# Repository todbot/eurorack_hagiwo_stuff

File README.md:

# eurorack_hagiwo_stuff

So far just a PCB version of ["additive_vco"](https://note.com/solder_state/n/n30b3a8737b1e)

Here's a little demo video of it in action:

https://user-images.githubusercontent.com/274093/197078909-dfc56eac-acbd-4a94-ae75-ff46f5945844.mp4

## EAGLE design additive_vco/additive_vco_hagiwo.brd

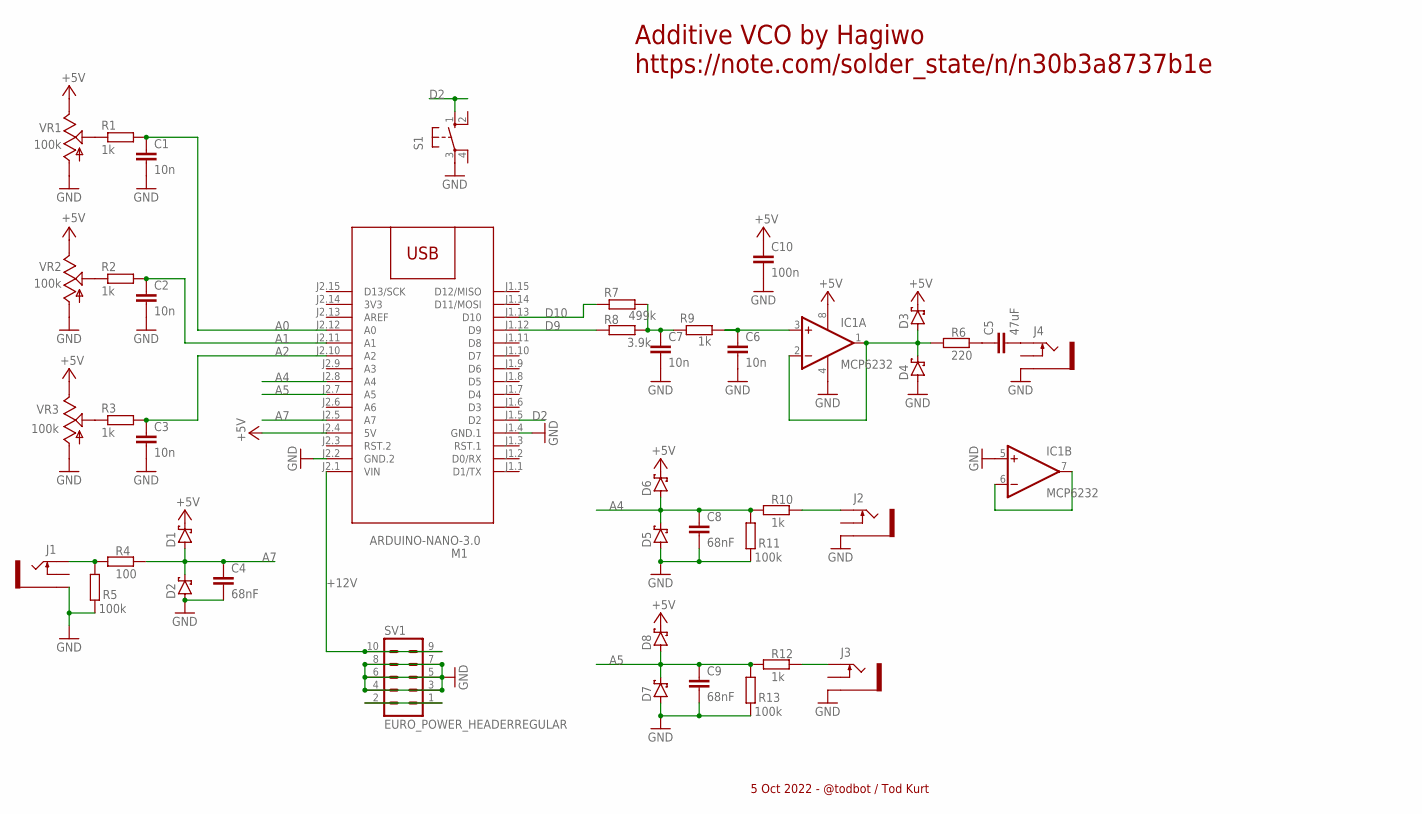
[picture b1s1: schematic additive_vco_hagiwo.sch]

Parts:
C1, C2, C3, C6, C7: 10n; C025-025X050
C4, C8, C9: 68nF; C025-025X050
C5: 47uF; C025-025X050
C10: 100n; C025-025X050
D1, D2, D3, D4, D5, D6, D7, D8: SCHOTTKY-DIODEDO35-7; DO35-7
IC1: MCP6232; DIL08
J1, J2, J3, J4: THONKICONNNEW; WQP-PJ301M-12_JACK
M1: ARDUINO-NANO-3.0
R1, R2, R3, R9: 1k; 0204V
R4: 100; 0204/5
R5, R11, R13: 100k; 0204/5
R6: 220; 0204/5
R7: 499k; 0204V
R8: 3.9k; 0204V
R10, R12: 1k; 0204/5
S1: 10-XX; B3F-10XX
SV1: EURO_POWER_HEADERREGULAR; EURO_POWER_HEADER
VR1, VR2, VR3: 100k; 9MM_SNAP-IN_POT

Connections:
3V3: M1.J2.14 (3V3)
+5V: C10.1, D1.C, D3.C, D6.C, D8.C, IC1.8 (V+), M1.J2.4 (5V), VR1.3 (E), VR2.3 (E), VR3.3 (E)
+12V: M1.J2.1 (VIN), SV1.9, SV1.10
A0: C1.1, M1.J2.12 (A0), R1.2
A1: C2.1, M1.J2.11 (A1), R2.2
A2: C3.1, M1.J2.10 (A2), R3.2
A4: C8.1, D5.C, D6.A, M1.J2.8 (A4), R10.1, R11.2
A5: C9.1, D7.C, D8.A, M1.J2.7 (A5), R12.1, R13.2
A7: C4.1, D1.A, D2.C, M1.J2.5 (A7), R4.2
D2: M1.J1.5 (D2), S1.1 (S)
D9: M1.J1.12 (D9), R8.1
D10: M1.J1.13 (D10), R7.1
GND: C1.2, C2.2, C3.2, C4.2, C6.2, C7.2, C8.2, C9.2, C10.2, D2.A, D4.A, D5.A, D7.A, IC1.4 (V-), IC1.5 (+IN), J1.P$3_SLEEVE (SLEEVE), J2.P$3_SLEEVE (SLEEVE), J3.P$3_SLEEVE (SLEEVE), J4.P$3_SLEEVE (SLEEVE), M1.J1.4 (GND.1), M1.J2.2 (GND.2), R5.1, R11.1, R13.1, S1.3, SV1.3, SV1.4, SV1.5, SV1.6, SV1.7, SV1.8, VR1.1 (A), VR2.1 (A), VR3.1 (A)
unnamed: R1.1, VR1.2 (S)
unnamed: R2.1, VR2.2 (S)
unnamed: R3.1, VR3.2 (S)
unnamed: C5.1, R6.2
unnamed: C5.2, J4.P$1_TIP (TIP)
unnamed: D3.A, D4.C, IC1.1 (OUT), IC1.2 (-IN), R6.1
unnamed: J1.P$1_TIP (TIP), R4.1, R5.2
unnamed: C6.1, IC1.3 (+IN), R9.2
unnamed: C7.1, R7.2, R8.2, R9.1
unnamed: SV1.1, SV1.2
unnamed: J2.P$1_TIP (TIP), R10.2
unnamed: IC1.6 (-IN), IC1.7 (OUT)
unnamed: J3.P$1_TIP (TIP), R12.2

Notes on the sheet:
Additive VCO by Hagiwo https://note.com/solder_state/n/n30b3a8737b1e
5 Oct 2022 - @todbot / Tod Kurt

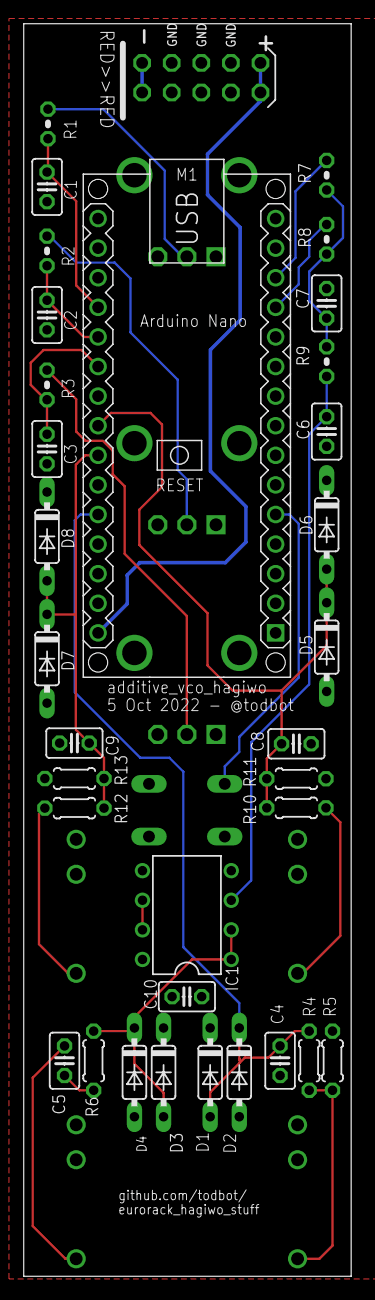
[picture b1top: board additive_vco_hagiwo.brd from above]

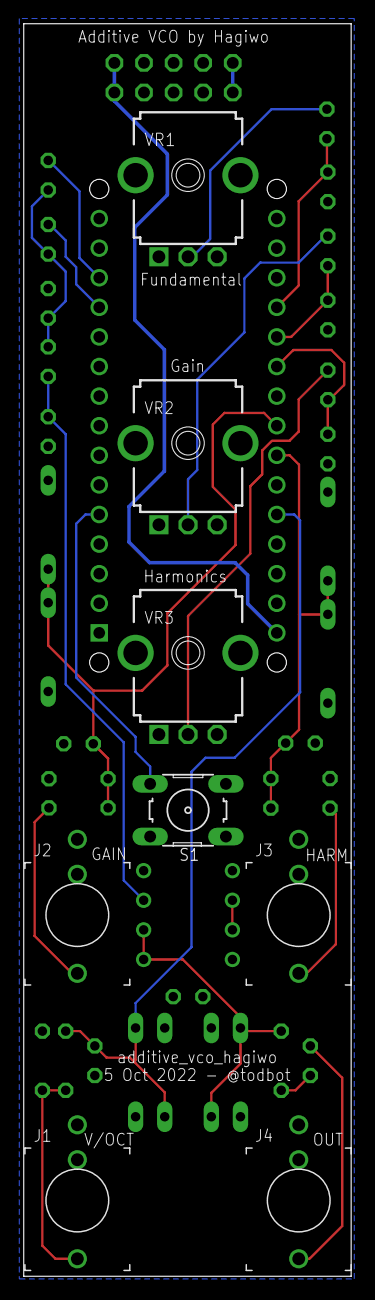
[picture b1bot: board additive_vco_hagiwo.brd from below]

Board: 2 copper layers, 28.1 x 107.5 mm, 42 parts (8 on the bottom side), 25 nets.

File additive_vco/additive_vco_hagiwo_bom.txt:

Partlist exported from /Users/tod/projects/synth/eurorack_hagiwo_stuff/additive_vco/additive_vco_hagiwo.sch at 10/19/22 3:58 P

Qty Value                    Device                   Package            Parts                          Description
1                            10-XX                    B3F-10XX           S1                             OMRON SWITCH
8                            SCHOTTKY-DIODEDO35-7     DO35-7             D1, D2, D3, D4, D5, D6, D7, D8 Schottky Diode
1   100                      R-EU_0204/5              0204/5             R4                             RESISTOR, European symbol
3   100k                     9MM_SNAP-IN_POT_         9MM_SNAP-IN_POT    VR1, VR2, VR3                  9mm vertical snap-in pot, Alpha / Panasonic style
3   100k                     R-EU_0204/5              0204/5             R5, R11, R13                   RESISTOR, European symbol
1   100n                     C-EU025-025X050          C025-025X050       C10                            CAPACITOR, European symbol
5   10n                      C-EU025-025X050          C025-025X050       C1, C2, C3, C6, C7             CAPACITOR, European symbol
6   1k                       R-EU_0204/2V             0204V              R1, R2, R3, R9, R10, R12       RESISTOR, European symbol
1   220                      R-EU_0204/5              0204/5             R6                             RESISTOR, European symbol
1   3.9k                     R-EU_0204/2V             0204V              R8                             RESISTOR, European symbol
1   47uF                     C-EU025-025X050          C025-025X050       C5                             CAPACITOR, European symbol
1   499k                     R-EU_0204/2V             0204V              R7                             RESISTOR, European symbol
3   68nF                     C-EU025-025X050          C025-025X050       C4, C8, C9                     CAPACITOR, European symbol
1   ARDUINO-NANO-3.0         ARDUINO-NANO-3.0         ARDUINO-NANO-3.0   M1                             Arduino Nano 3.0 and compatible devices
1   EURO_POWER_HEADERREGULAR EURO_POWER_HEADERREGULAR EURO_POWER_HEADER  SV1                            Power Header
1   MCP6232                  MCP602P                  DIL08              IC1                            Single Op Amp 2.7V to 6.0V Single Supply CMOS
4   THONKICONNNEW            THONKICONNNEW            WQP-PJ301M-12_JACK J1, J2, J3, J4                 3.5mm socket for Eurorack modular synths

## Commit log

2022-10-06 first
2022-10-07 skooch layout a bit to USB and power work out
2022-10-07 first cut at front panel
2022-10-07 better front panel
2022-10-08 submit to pcb fab
2022-10-08 panel artwork
2022-10-17 fix too panel pot holes. wth tod?
2022-10-20 arduino code verified works
2022-10-20 pics
2022-10-20 add demo video

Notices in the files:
parts and their libraries:
diy-modules: Released under the Creative Commons Attribution 4.0 International License: http://creativecommons.org/licenses/by/4.0
